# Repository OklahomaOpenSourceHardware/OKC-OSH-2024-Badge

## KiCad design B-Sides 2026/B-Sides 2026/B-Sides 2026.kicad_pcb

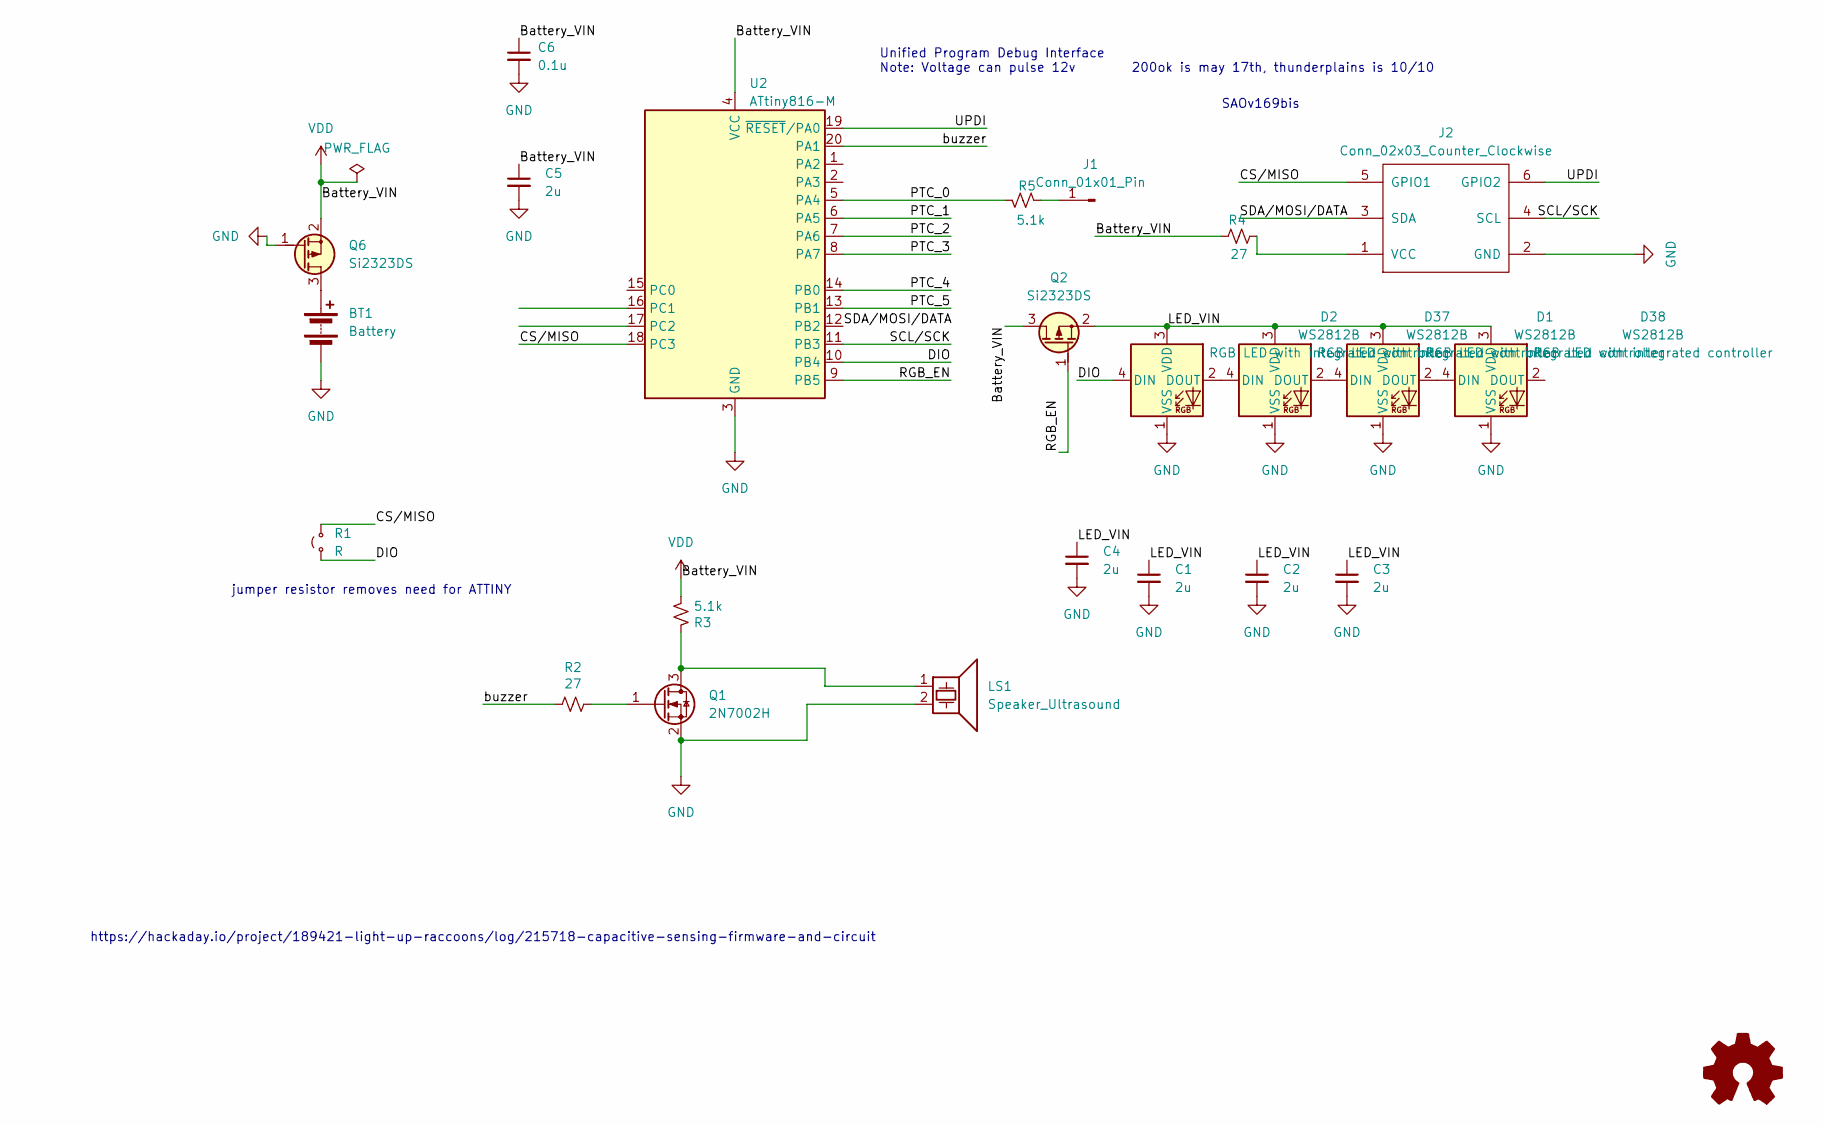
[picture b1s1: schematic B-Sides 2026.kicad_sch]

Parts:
BT1: Battery; BatteryHolder_Keystone_3008_1x2450; LCSC C964845
C1, C2, C3, C4, C5: 2u; C_0402_1005Metric; LCSC C12530
C6: 0.1u; C_0402_1005Metric; LCSC C1525
D1, D2, D37, D38: WS2812B; WS2812B-4020; LCSC C3647024
J1: Conn_01x01_Pin; Swoosh
J2: Conn_02x03_Counter_Clockwise; Simple_Addon_v2-BADGE-2x3; LCSC C92272
LS1: Speaker_Ultrasound; Buzzer_Murata_PKLCS1212E; LCSC C49246959
Q1: 2N7002H; SOT-23; LCSC C81445
Q2, Q6: Si2323DS; SOT-23; LCSC C347476
R1: R; SolderJumper-2_P1.3mm_Open_TrianglePad1.0x1.5mm
R2, R4: 27; R_0402_1005Metric; Manufacturer_Part_Number RK73B1JTTDD270J; Mouser Part Number 660-RK73B1JTTDD270J
R3, R5: 5.1k; R_0402_1005Metric; Manufacturer_Part_Number CR0603-FX-5101ELF; Mouser Part Number 652-CR0603FX-5101ELF
U2: ATtiny816-M; VQFN-20-1EP_3x3mm_P0.4mm_EP1.7x1.7mm; LCSC C2052778

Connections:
/CS/MISO: J2.5 (GPIO1), R1.2 (B), U2.18 (PC3)
/DIO: D2.4 (DIN), R1.1 (A), U2.10 (PB4)
/LED_VIN: C1.1, C2.1, C3.1, C4.1, D1.3 (VDD), D2.3 (VDD), D37.3 (VDD), D38.3 (VDD), Q2.2 (S)
/PTC_0: R5.2, U2.5 (PA4)
/PTC_1: U2.6 (PA5)
/PTC_2: U2.7 (PA6)
/PTC_3: U2.8 (PA7)
/PTC_4: U2.14 (PB0)
/PTC_5: U2.13 (PB1)
/RGB_EN: Q2.1 (G), U2.9 (PB5)
/SCL/SCK: J2.4 (SCL), U2.11 (PB3)
/SDA/MOSI/DATA: J2.3 (SDA), U2.12 (PB2)
/UPDI: J2.6 (GPIO2), U2.19 (~RESET/PA0)
/buzzer: R2.1, U2.20 (PA1)
GND: BT1.2 (-), C1.2, C2.2, C3.2, C4.2, C5.2, C6.2, D1.1 (VSS), D2.1 (VSS), D37.1 (VSS), D38.1 (VSS), J2.2 (GND), LS1.2, Q1.2 (S), Q6.1 (G), U2.3 (GND), U2.21 (GND)
unnamed: BT1.1 (+), Q6.3 (D)
unnamed: D1.4 (DIN), D37.2 (DOUT)
unnamed: D1.2 (DOUT), D38.4 (DIN)
unnamed: D2.2 (DOUT), D37.4 (DIN)
unnamed: J1.1, R5.1
unnamed: J2.1 (VCC), R4.2
unnamed: LS1.1, Q1.3 (D), R3.1
unnamed: Q1.1 (G), R2.2
VDD: C5.1, C6.1, Q2.3 (D), Q6.2 (S), R3.2, R4.1, U2.4 (VCC)

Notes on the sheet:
https://hackaday.io/project/189421-light-up-raccoons/log/215718-capacitive-sensing-firmware-and-circuit
200ok is may 17th, thunderplains is 10/10
jumper resistor removes need for ATTINY
Unified Program Debug Interface Note: Voltage can pulse 12v
SAOv169bis

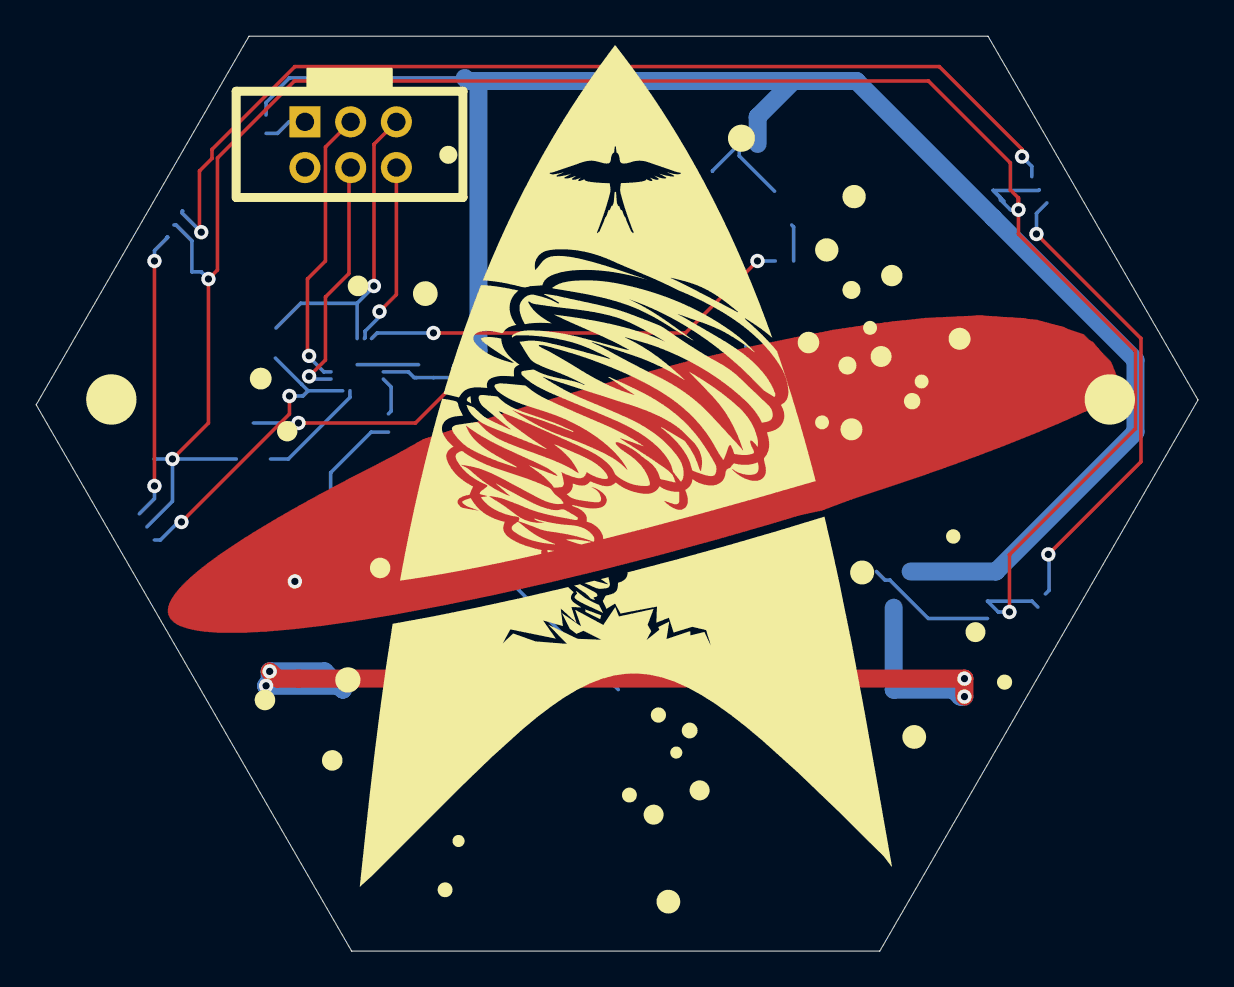
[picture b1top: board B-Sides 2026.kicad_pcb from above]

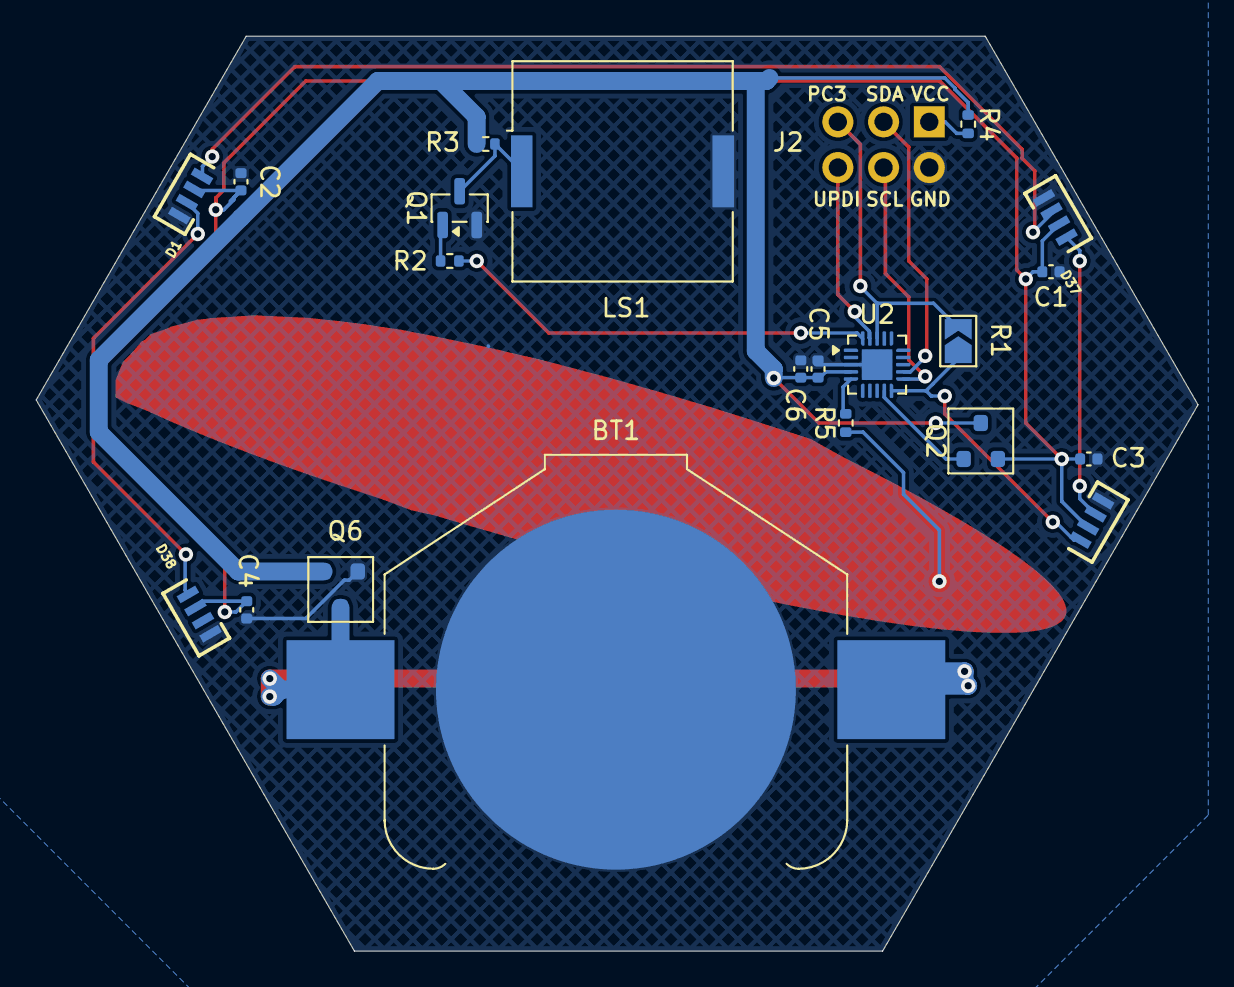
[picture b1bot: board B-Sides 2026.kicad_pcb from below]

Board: 2 copper layers, 64.5 x 50.8 mm, 23 parts (21 on the bottom side), 19 nets.

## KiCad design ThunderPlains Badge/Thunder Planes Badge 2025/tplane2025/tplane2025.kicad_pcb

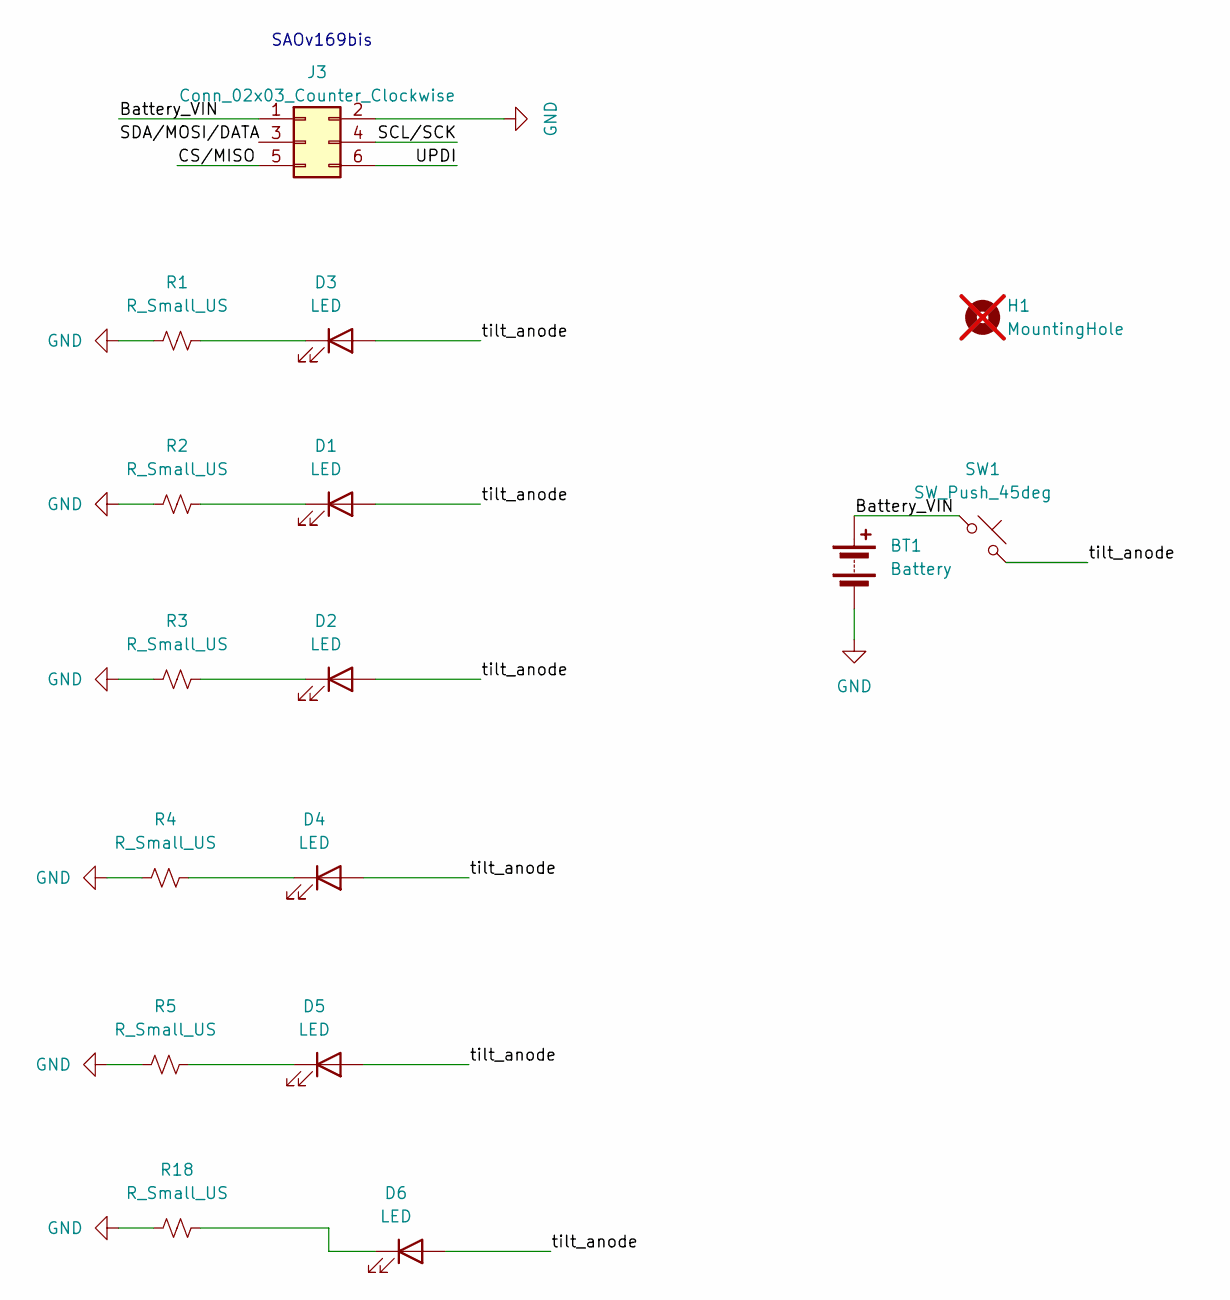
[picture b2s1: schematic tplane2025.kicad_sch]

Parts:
BT1: Battery; BatteryHolder_Keystone_3008_1x2450; LCSC C964845
D1, D2, D3, D4, D5, D6: LED; LED_D3.0mm_Horizontal_O1.27mm_Z2.0mm_BiDir
H1: MountingHole; MountingHole_3.2mm_M3; not fitted
J3: Conn_02x03_Counter_Clockwise; PinHeader_2x03_P2.54mm_Vertical
R1, R2, R3, R4, R5, R18: R_Small_US; R_1206_3216Metric
SW1: SW_Push_45deg; LED_Rectangular_W5.0mm_H2.0mm_Horizontal_O6.35mm_Z5.0mm

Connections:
/Battery_VIN: BT1.1 (+), J3.1, SW1.1
/CS/MISO: J3.5
/SCL/SCK: J3.4
/UPDI: J3.6
/tilt_anode: D1.2 (A), D2.2 (A), D3.2 (A), D4.2 (A), D5.2 (A), D6.2 (A), SW1.2
GND: BT1.2 (-), J3.2, R1.1, R2.1, R3.1, R4.1, R5.1, R18.1
unnamed: D1.1 (K), R2.2
unnamed: D2.1 (K), R3.2
unnamed: D3.1 (K), R1.2
unnamed: D4.1 (K), R4.2
unnamed: D5.1 (K), R5.2
unnamed: D6.1 (K), R18.2

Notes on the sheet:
SAOv169bis

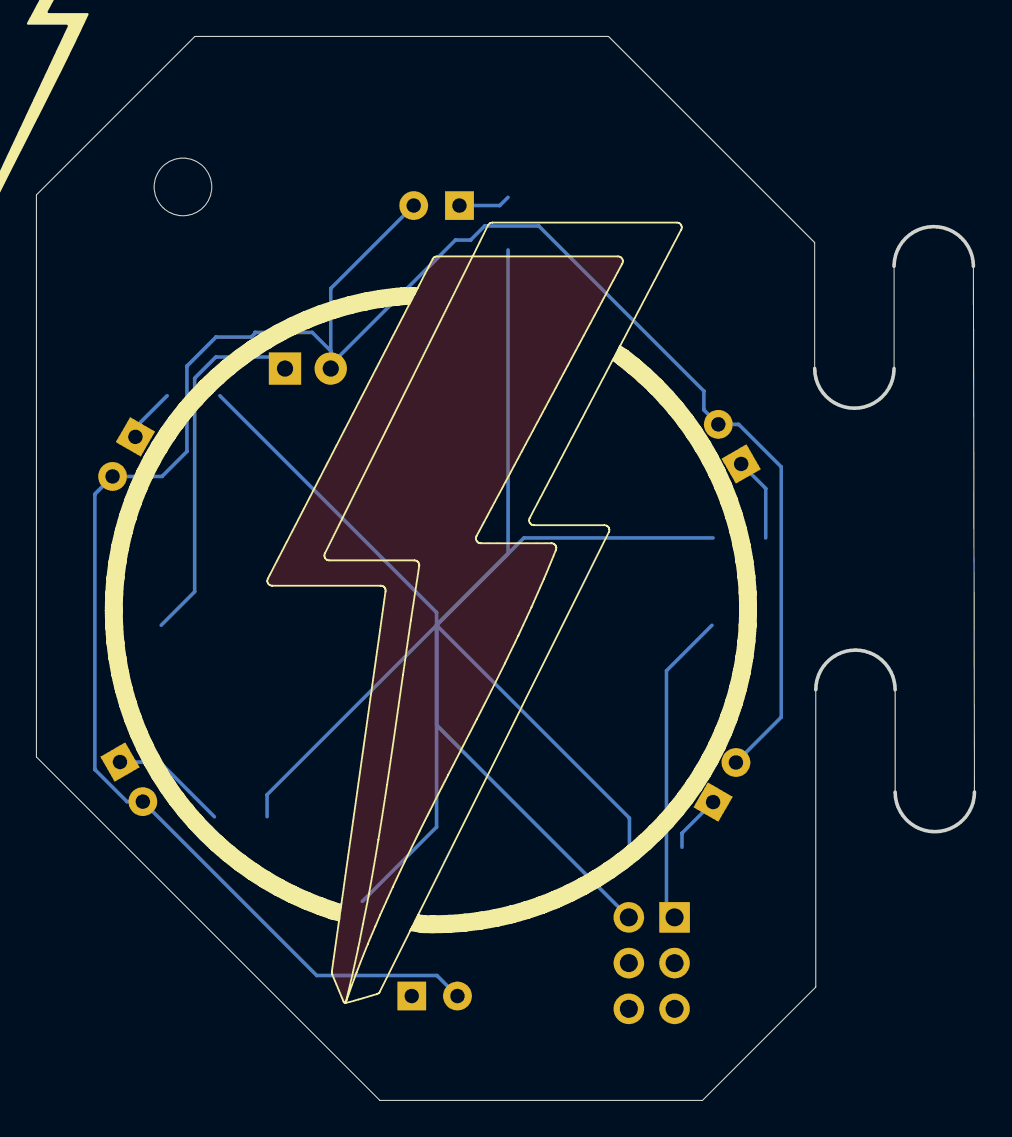
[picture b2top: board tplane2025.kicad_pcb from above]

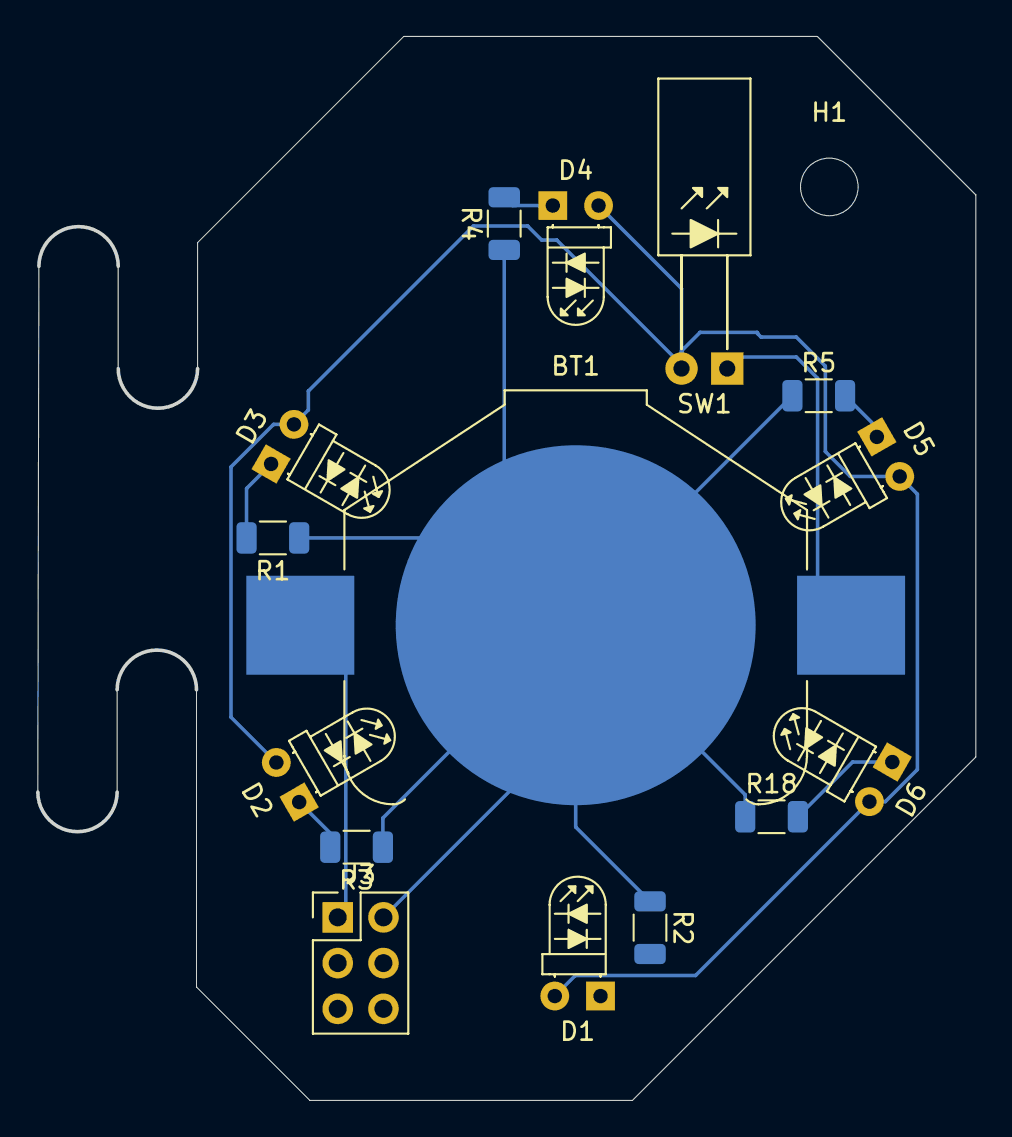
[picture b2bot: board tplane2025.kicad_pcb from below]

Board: 2 copper layers, 52.1 x 59.1 mm, 16 parts (16 on the bottom side), 9 nets.

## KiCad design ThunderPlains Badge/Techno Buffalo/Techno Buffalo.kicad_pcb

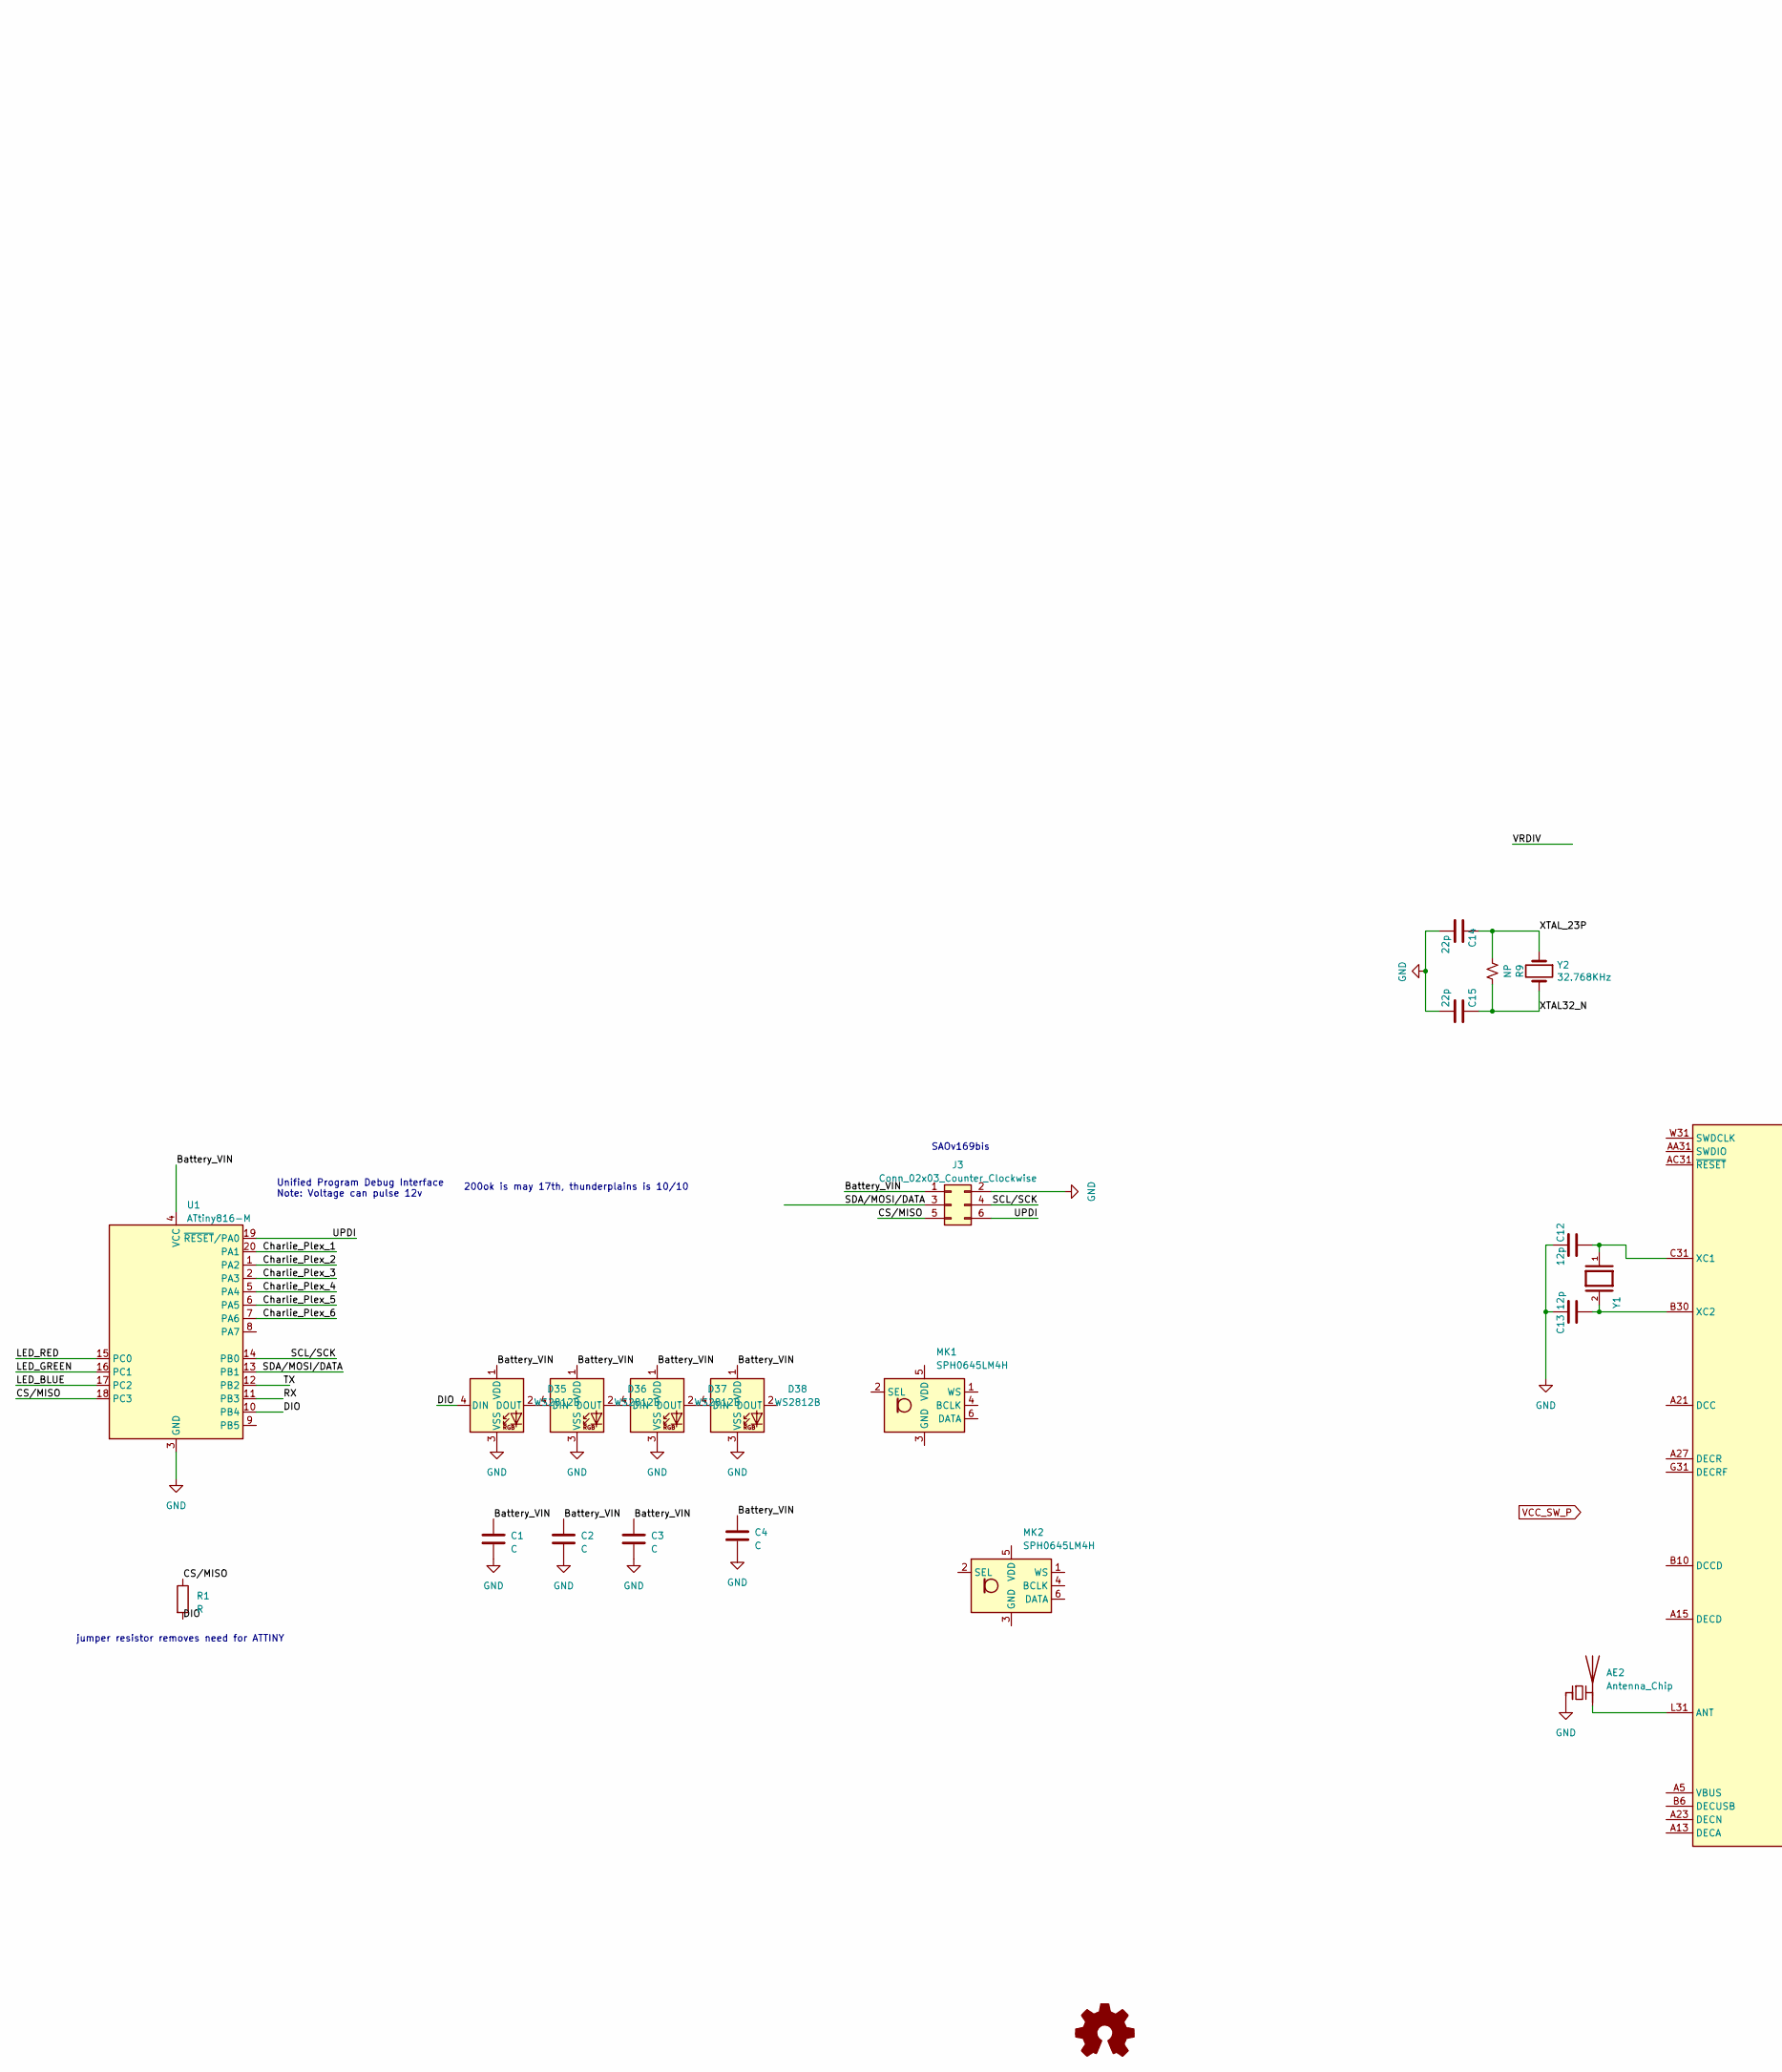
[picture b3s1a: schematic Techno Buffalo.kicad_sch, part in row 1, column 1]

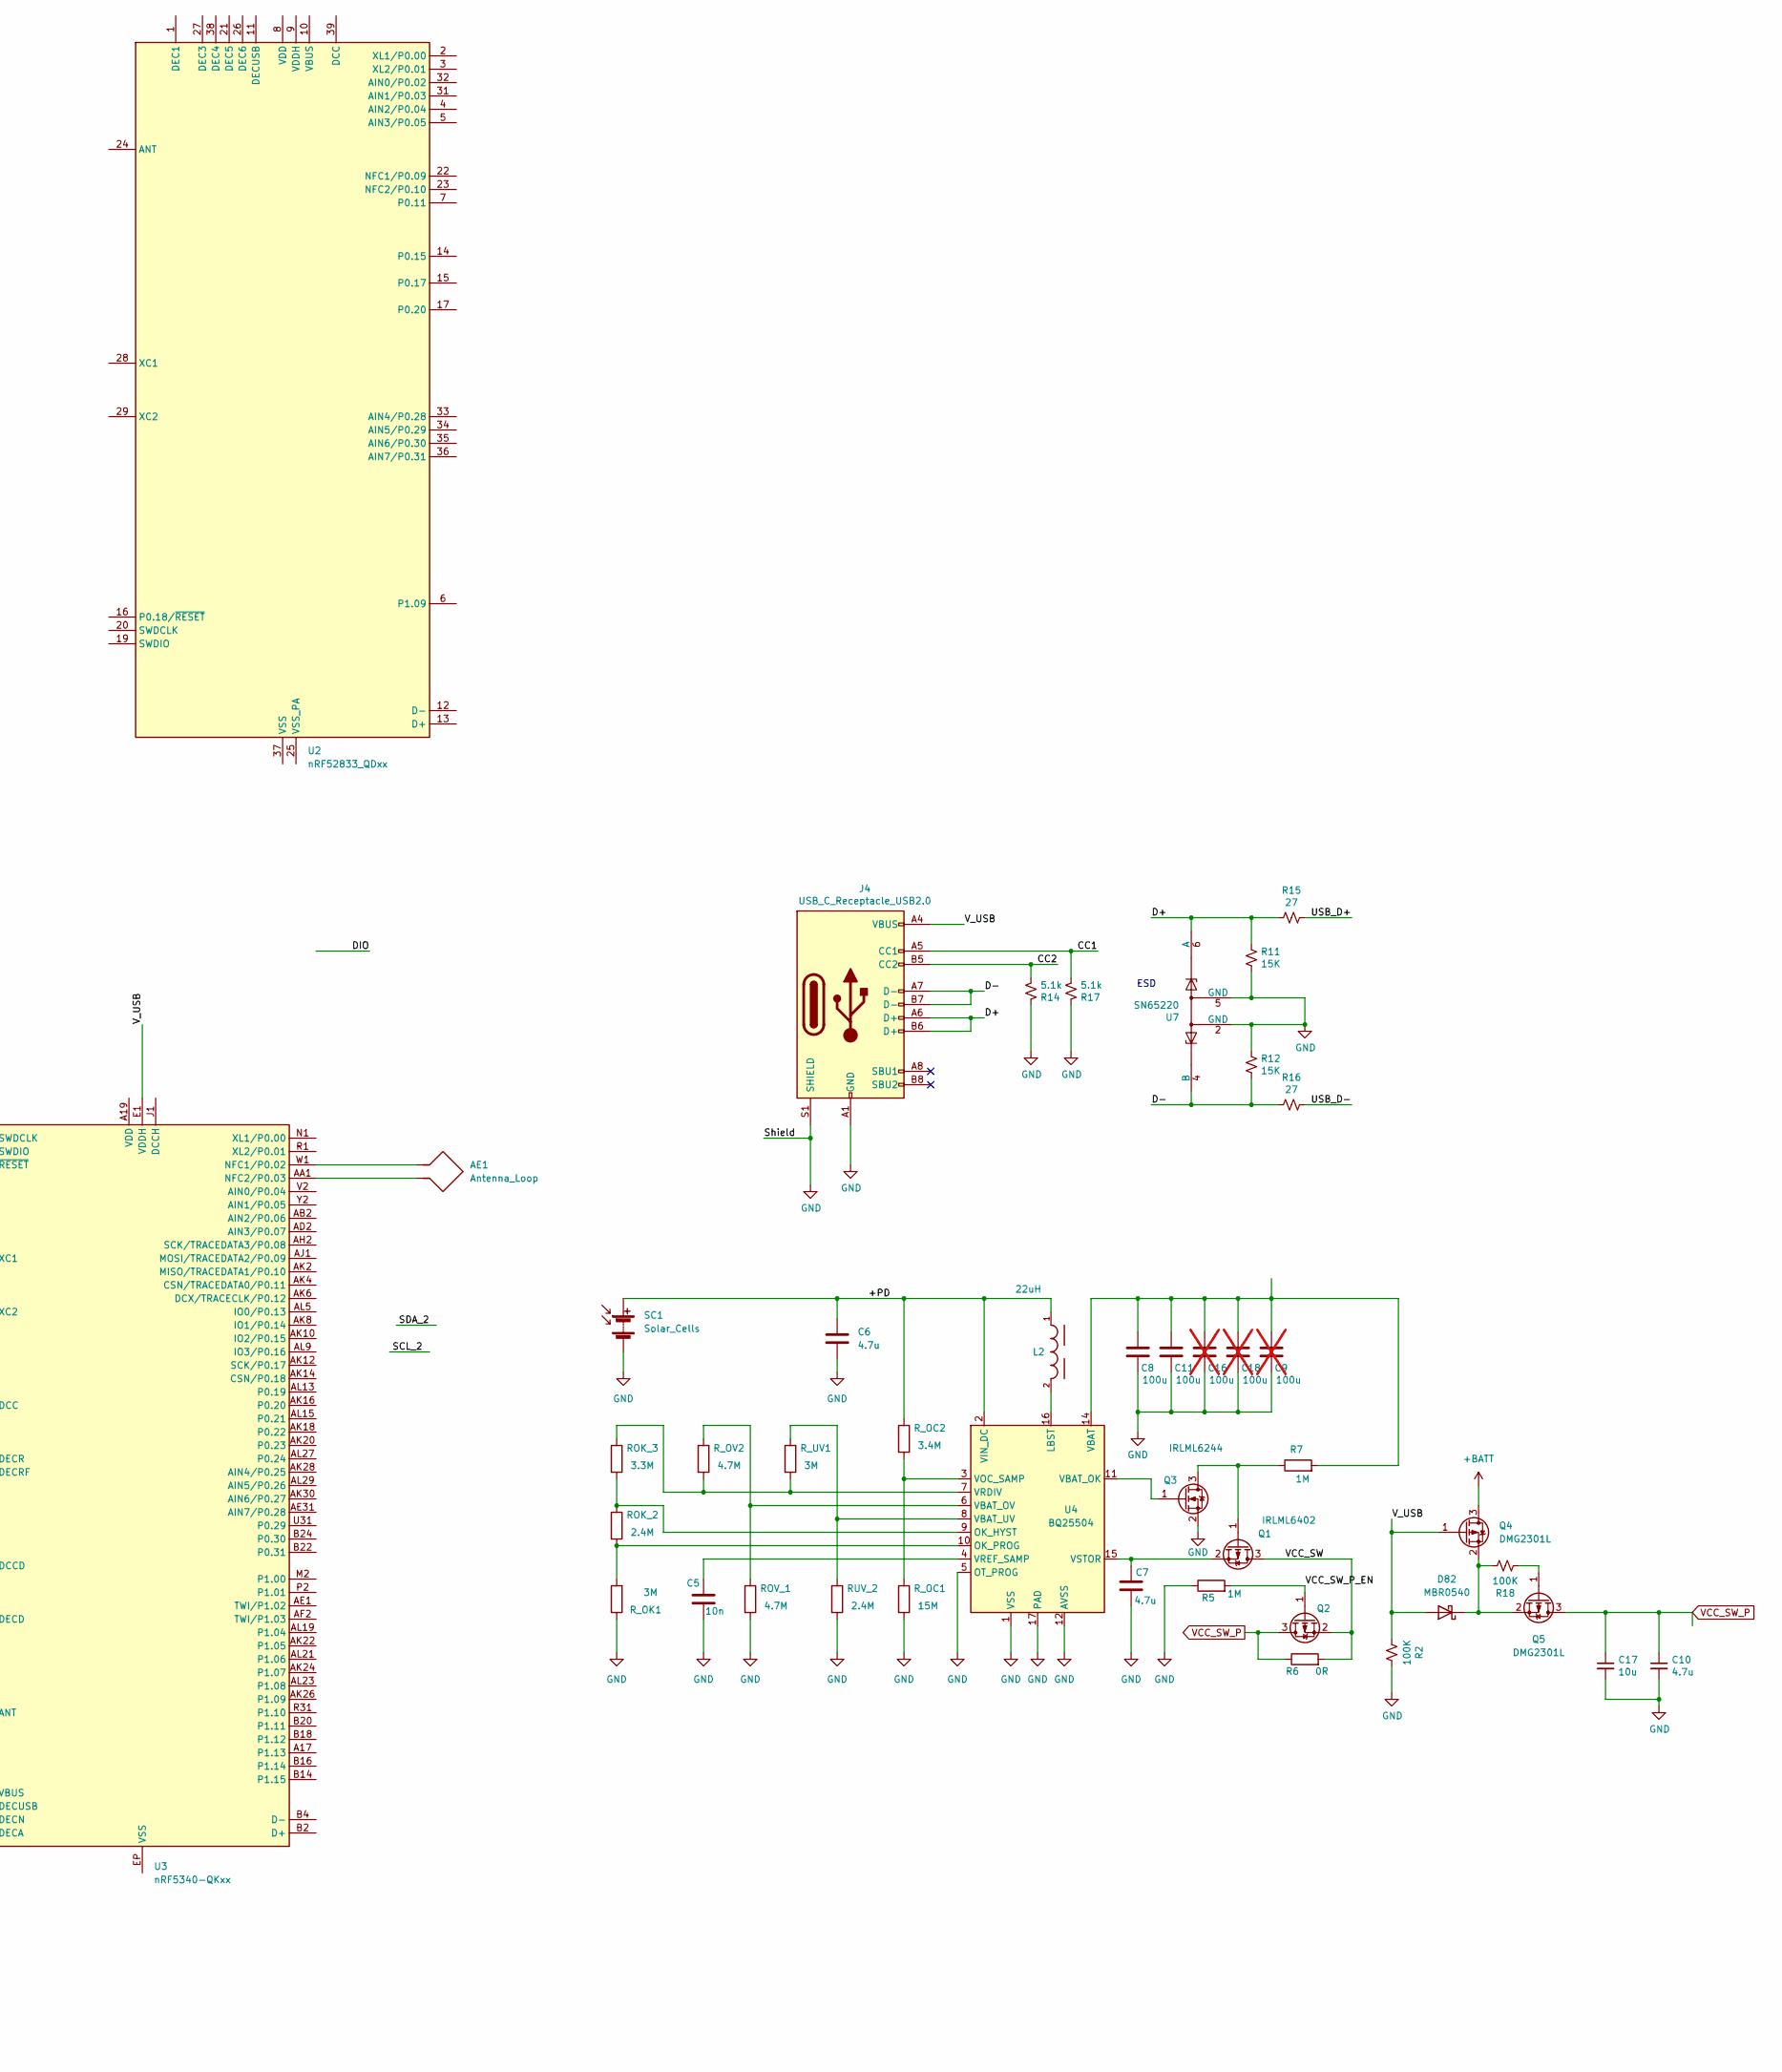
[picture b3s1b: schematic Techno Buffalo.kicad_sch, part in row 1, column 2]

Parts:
AE1: Antenna_Loop
AE2: Antenna_Chip
C1, C2, C3, C4: C; C_0603_1608Metric_Pad1.08x0.95mm_HandSolder
C5: 10n; C_0603_1608Metric_Pad1.08x0.95mm_HandSolder
C6, C7: 4.7u; C_0805_2012Metric_Pad1.18x1.45mm_HandSolder
C8, C11: 100u; C_1206_3216Metric_Pad1.33x1.80mm_HandSolder
C9, C16, C18: 100u; C_1206_3216Metric_Pad1.33x1.80mm_HandSolder; not fitted
C10: 4.7u; C_0805_2012Metric; Manufacturer_Part_Number JMK107C6475KA-T; Mouser Part Number 963-JMK107C6475KA-T
C12, C13: 12p; C_0603_1608Metric_Pad1.08x0.95mm_HandSolder
C14, C15: 22p; C_0805_2012Metric_Pad1.18x1.45mm_HandSolder
C17: 10u; C_1206_3216Metric; Manufacturer_Part_Number LMK212ABJ106MG-T; Mouser Part Number 963-LMK212ABJ106MG-T
D35, D36, D37, D38: WS2812B; WS2812B-4020
D82: MBR0540; D_SOD-123
J3: Conn_02x03_Counter_Clockwise; PinHeader_2x03_P2.54mm_Vertical
J4: USB_C_Receptacle_USB2.0; USB_C_Receptacle_HRO_TYPE-C-31-M-12; Manufacturer_Part_Number USB4105-GF-A; Mouser Part Number 640-USB4105-GF-A
L2: 22uH; WE-TPC_2828
MK1, MK2: SPH0645LM4H; Knowles_SPH0645LM4H-6_3.5x2.65mm
Q1, Q2: IRLML6402; SOT-23
Q3: IRLML6244; SOT-23
Q4, Q5: DMG2301L; SOT-23
R1: R; R_0603_1608Metric_Pad0.98x0.95mm_HandSolder
R2, R18: 100K; R_0402_1005Metric; Manufacturer_Part_Number ESR03EZPJ104; Mouser Part Number 755-ESR03EZPJ104
R5, R7: 1M; R_0603_1608Metric_Pad0.98x0.95mm_HandSolder
R6: 0R; R_0603_1608Metric_Pad0.98x0.95mm_HandSolder
R9: NP; R_0402_1005Metric; Manufacturer_Part_Number ESR03EZPJ103; Mouser Part Number 755-ESR03EZPJ103
R11, R12: 15K; R_0402_1005Metric; Manufacturer_Part_Number RC0603FR-1315KL; Mouser Part Number 603-RC0603FR-1315KL
R14, R17: 5.1k; R_0402_1005Metric; Manufacturer_Part_Number CR0603-FX-5101ELF; Mouser Part Number 652-CR0603FX-5101ELF
R15, R16: 27; R_0402_1005Metric; Manufacturer_Part_Number RK73B1JTTDD270J; Mouser Part Number 660-RK73B1JTTDD270J
ROK_2: 2.4M; R_0603_1608Metric_Pad0.98x0.95mm_HandSolder
ROK_3: 3.3M; R_0603_1608Metric_Pad0.98x0.95mm_HandSolder
ROV_1: 4.7M; R_0603_1608Metric_Pad0.98x0.95mm_HandSolder
RUV_2: 2.4M; R_0603_1608Metric_Pad0.98x0.95mm_HandSolder
R_OC1: 15M; R_0603_1608Metric_Pad0.98x0.95mm_HandSolder
R_OC2: 3.4M; R_0603_1608Metric_Pad0.98x0.95mm_HandSolder
R_OK1: 3M; R_0603_1608Metric_Pad0.98x0.95mm_HandSolder
R_OV2: 4.7M; R_0603_1608Metric_Pad0.98x0.95mm_HandSolder
R_UV1: 3M; R_0603_1608Metric_Pad0.98x0.95mm_HandSolder
SC1: Solar_Cells; AM-1606C
U1: ATtiny816-M; VQFN-20-1EP_3x3mm_P0.4mm_EP1.7x1.7mm
U2: nRF52833_QDxx; QFN-40-1EP_5x5mm_P0.4mm_EP3.6x3.6mm
U3: nRF5340-QKxx; Nordic_AQFN-94-1EP_7x7mm_P0.4mm
U4: BQ25504; VQFN-16-1EP_3x3mm_P0.5mm_EP1.68x1.68mm
U7: SN65220; SOT-23-6; Manufacturer_Part_Number SN65220DBVT; Mouser Part Number 595-SN65220DBVT
Y1: ABS07-32.768KHZ-T; XTAL_ABS07-32.768KHZ-T; PARTREV 08.19.15
Y2: 32.768KHz; Crystal_SMD_5032-2Pin_5.0x3.2mm_HandSoldering

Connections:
+BATT: Q4.3 (D)
/+PD: C6.1, L2.1, R_OC2.1, SC1.1 (+), U4.2 (VIN_DC)
/Battery_VIN: C1.1, C2.1, C3.1, C4.1, D35.1 (VDD), D36.1 (VDD), D37.1 (VDD), D38.1 (VDD), J3.1, U1.4 (VCC)
/CC1: J4.A5 (CC1), R17.2
/CC2: J4.B5 (CC2), R14.2
/CS/MISO: J3.5, R1.1, U1.18 (PC3)
/Charlie_Plex_1: U1.20 (PA1)
/Charlie_Plex_2: U1.1 (PA2)
/Charlie_Plex_3: U1.2 (PA3)
/Charlie_Plex_4: U1.5 (PA4)
/Charlie_Plex_5: U1.6 (PA5)
/Charlie_Plex_6: U1.7 (PA6)
/D+: J4.A6 (D+), J4.B6 (D+), R11.1, R15.1, U7.1, U7.6 (A)
/D-: J4.A7 (D-), J4.B7 (D-), R12.2, R16.1, U7.3, U7.4 (B)
/DIO: D35.4 (DIN), R1.2, U1.10 (PB4)
/LED_BLUE: U1.17 (PC2)
/LED_GREEN: U1.16 (PC1)
/LED_RED: U1.15 (PC0)
/RX: U1.11 (PB3)
/SCL/SCK: J3.4, U1.14 (PB0)
/SDA/MOSI/DATA: J3.3, U1.13 (PB1)
/TX: U1.12 (PB2)
/UPDI: J3.6, U1.19 (~RESET/PA0)
/USB_D+: R15.2
/USB_D-: R16.2
/VCC_SW: Q1.3 (D), Q2.2 (S), R6.2
/VCC_SW_P_EN: Q2.1 (G), R5.2
/V_USB: D82.2 (A), J4.A4 (VBUS), J4.A9 (VBUS), J4.B4 (VBUS), J4.B9 (VBUS), Q4.1 (G), R2.2, U3.E1 (VDDH)
/XTAL32_N: C15.1, R9.1, Y2.2
/XTAL_23P: C14.1, R9.2, Y2.1
GND: AE2.1 (FEED), C1.2, C2.2, C3.2, C4.2, C5.1, C6.2, C7.2, C8.2, C9.2, C10.2, C11.2, C12.1, C13.1, C14.2, C15.2, C16.2, C17.2, C18.2, D35.3 (VSS), D36.3 (VSS), D37.3 (VSS), D38.3 (VSS), J3.2, J4.A1 (GND), J4.A12 (GND), J4.B1 (GND), J4.B12 (GND), J4.S1 (SHIELD), Q3.2 (S), R2.1, R5.1, R11.2, R12.1, R14.1, R17.1, ROV_1.2, RUV_2.2, R_OC1.2, R_OK1.1, SC1.2 (-), U1.3 (GND), U1.21 (GND), U4.1 (VSS), U4.5 (OT_PROG), U4.12 (AVSS), U4.13 (VSS), U4.17 (PAD), U7.2 (GND), U7.5 (GND)
unnamed: AE2.2 (PCB_Trace), U3.L31 (ANT)
unnamed: D35.2 (DOUT), D36.4 (DIN)
unnamed: D36.2 (DOUT), D37.4 (DIN)
unnamed: D37.2 (DOUT), D38.4 (DIN)
unnamed: D82.1 (K), Q4.2 (S), Q5.2 (S), R18.1
unnamed: Q1.1 (G), Q3.3 (D), R7.1
unnamed: C7.1, Q1.2 (S), U4.15 (VSTOR)
unnamed: Q3.1 (G), U4.11 (VBAT_OK)
unnamed: Q5.1 (G), R18.2
unnamed: U2.8 (VDD), U2.18 (VDD), U2.30 (VDD), U2.40 (VDD)
unnamed: U2.37 (VSS), U2.41 (VSS)
unnamed: AE1.1, U3.W1 (NFC1/P0.02)
unnamed: AE1.2, U3.AA1 (NFC2/P0.03)
unnamed: U3.A19 (VDD), U3.AC1 (VDD), U3.AG1 (VDD), U3.AJ31 (VDD), U3.AL3 (VDD), U3.AL7 (VDD), U3.AL11 (VDD), U3.AL17 (VDD), U3.AL25 (VDD), U3.B8 (VDD), U3.B28 (VDD), U3.C1 (VDD), U3.E31 (VDD), U3.L1 (VDD), U3.N31 (VDD), U3.U1 (VDD)
unnamed: C12.2, U3.C31 (XC1), Y1.1
unnamed: C13.2, U3.B30 (XC2), Y1.2
unnamed: L2.2, U4.16 (LBST)
unnamed: ROK_2.1, ROK_3.2, U4.9 (OK_HYST)
unnamed: ROK_2.2, R_OK1.2, U4.10 (OK_PROG)
unnamed: C8.1, C9.1, C11.1, C16.1, C18.1, R7.2, U4.14 (VBAT)
unnamed: ROV_1.1, R_OV2.1, U4.6 (VBAT_OV)
unnamed: RUV_2.1, R_UV1.1, U4.8 (VBAT_UV)
unnamed: R_OC1.1, R_OC2.2, U4.3 (VOC_SAMP)
unnamed: ROK_3.1, R_OV2.2, R_UV1.2, U4.7 (VRDIV)
unnamed: C5.2, U4.4 (VREF_SAMP)
VCC_SW_P: C10.1, C17.1, Q2.3 (D), Q5.3 (D), R6.1

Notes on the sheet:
jumper resistor removes need for ATTINY
200ok is may 17th, thunderplains is 10/10
Unified Program Debug Interface Note: Voltage can pulse 12v
SAOv169bis
ESD
